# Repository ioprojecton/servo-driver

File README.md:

# servo-driver
Low current servo driver.
Can work both 3.3/5v supplies.
Input current needed to drive hobby servo <0.1ma.
Has separate control of power supply to servo .
Dual power support - regulated and unregulated.

Board can run up to 1.3khz speed (tested).

Suitable to drive 5v hobby servos with up to 1.25A stall current.

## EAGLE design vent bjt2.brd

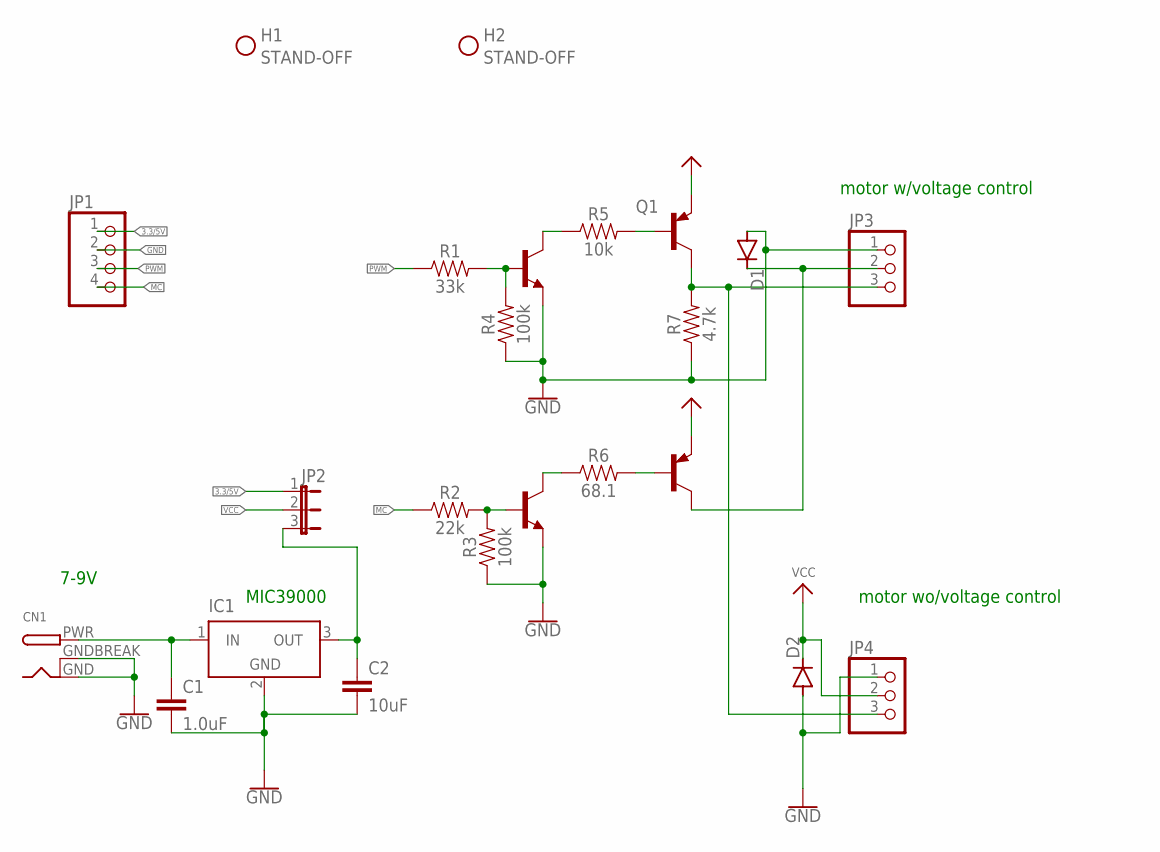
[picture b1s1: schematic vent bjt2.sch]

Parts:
C1: 1.0uF; 0603
C2: 10uF; 0603
C945: C945; TO92-ECB
CN1: DCBARRELPTH; DCJACK_2MM_PTH
D1, D2: 1N4148DO35-7; DO35-7
H1, H2: STAND-OFF
IC1: LT1129CST5; SOT223
JP1: PINHD-1X4; 1X04
JP2: JP2E; JP2
JP3, JP4: PINHD-1X3; 1X03
Q1: 2N2907; TO92-EBC-OVAL
R1: 33k; 0603
R2: 22k; 0603
R3, R4: 100k; 0603
R5: 10k; 0603
R6: 68.1; 0603
R7: 4.7k; 0603
S8550: S8550; TO92-EBC-OVAL
T1: S9018; TO92-EBC-OVAL

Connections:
3.3/5V: JP1.1, JP2.1
GND: C1.2, C2.2, C945.E, CN1.GND, CN1.GNDBREAK, D1.A, D2.A, IC1.2 (GND), IC1.4 (GND), JP1.2, JP3.1, JP4.1, R3.1, R4.1, R7.1, T1.E
MC: JP1.4, R2.1
unnamed: R1.2, R4.2, T1.B
unnamed: D1.C, JP3.2, S8550.C
unnamed: R5.1, T1.C
unnamed: Q1.B, R5.2
unnamed: JP3.3, JP4.3, Q1.C, R7.2
unnamed: C945.B, R2.2, R3.2
unnamed: C1.1, CN1.PWR, IC1.1 (IN)
unnamed: C945.C, R6.1
unnamed: R6.2, S8550.B
unnamed: C2.1, IC1.3 (OUT), JP2.3
PWM: JP1.3, R1.1
VCC: D2.C, JP2.2, JP4.2, Q1.E, S8550.E

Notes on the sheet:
motor w/voltage control
motor wo/voltage control
7-9V
MIC39000

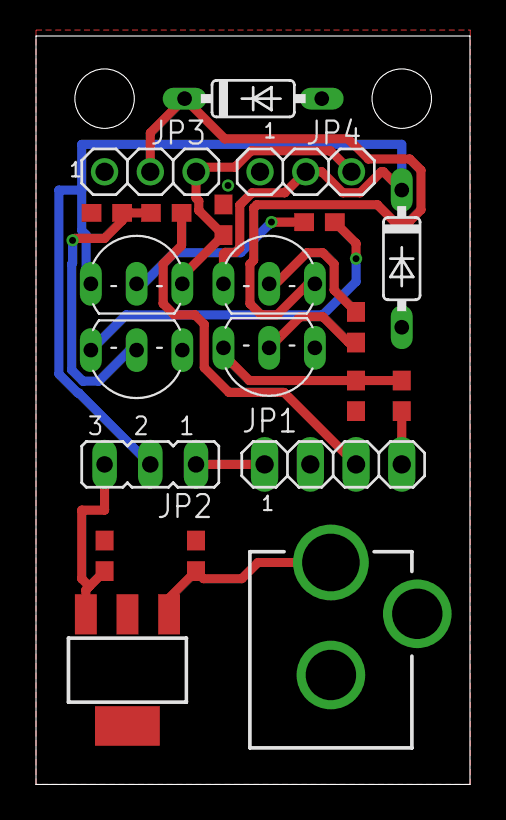
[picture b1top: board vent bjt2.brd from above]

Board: 2 copper layers, 24.1 x 41.6 mm, 23 parts (0 on the bottom side), 15 nets.

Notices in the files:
parts and their libraries:
SparkFun-Capacitors: Licensing: Creative Commons ShareAlike 4.0 International - https://creativecommons.org/licenses/by-sa/4.0
